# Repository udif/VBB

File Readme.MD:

VBB - A VCC Breakout Board
==========================
This board is intended as a VCC breakout board. It supports the following features:
* A wide array of connectors: USB A, B, Micro, Mini, DC plug, Banana Plug, screw terminal.
* While GND is always connected among all connectors, D+/D-/VCC are all switchable via pins.
* Banana plug dimensions match the front panel of Arachnid Lab's Re:Load Pro, and can be mounted directly on it, if one wishes.
* USB-A footprint can be soldered with either a male or female USB-A plug.

Possible uses:
--------------
1. Current measurements by inserting the Banana Plugs in the VCC path between any two connectors.
2. Power supply measurements using standard connectors (USB mini, micro, DC barrel jack) with Re:Load Pro 
3. Controlling of USB D+/D-, either disconnecting it to prevent a data connection, or biasing it with resistors to select a specific charging mode. Some Combinations, such as inserting VBB with two USB-A plugs (male+female) may require 2 PCBs.

TBD
---
* Add VCC/GND/D+/D- marks on the bottom side header pins.
* Possibly add mounting holes
* Next revision will be narrow and long, and support two independent USB-A connectors (male+female), one on each side.

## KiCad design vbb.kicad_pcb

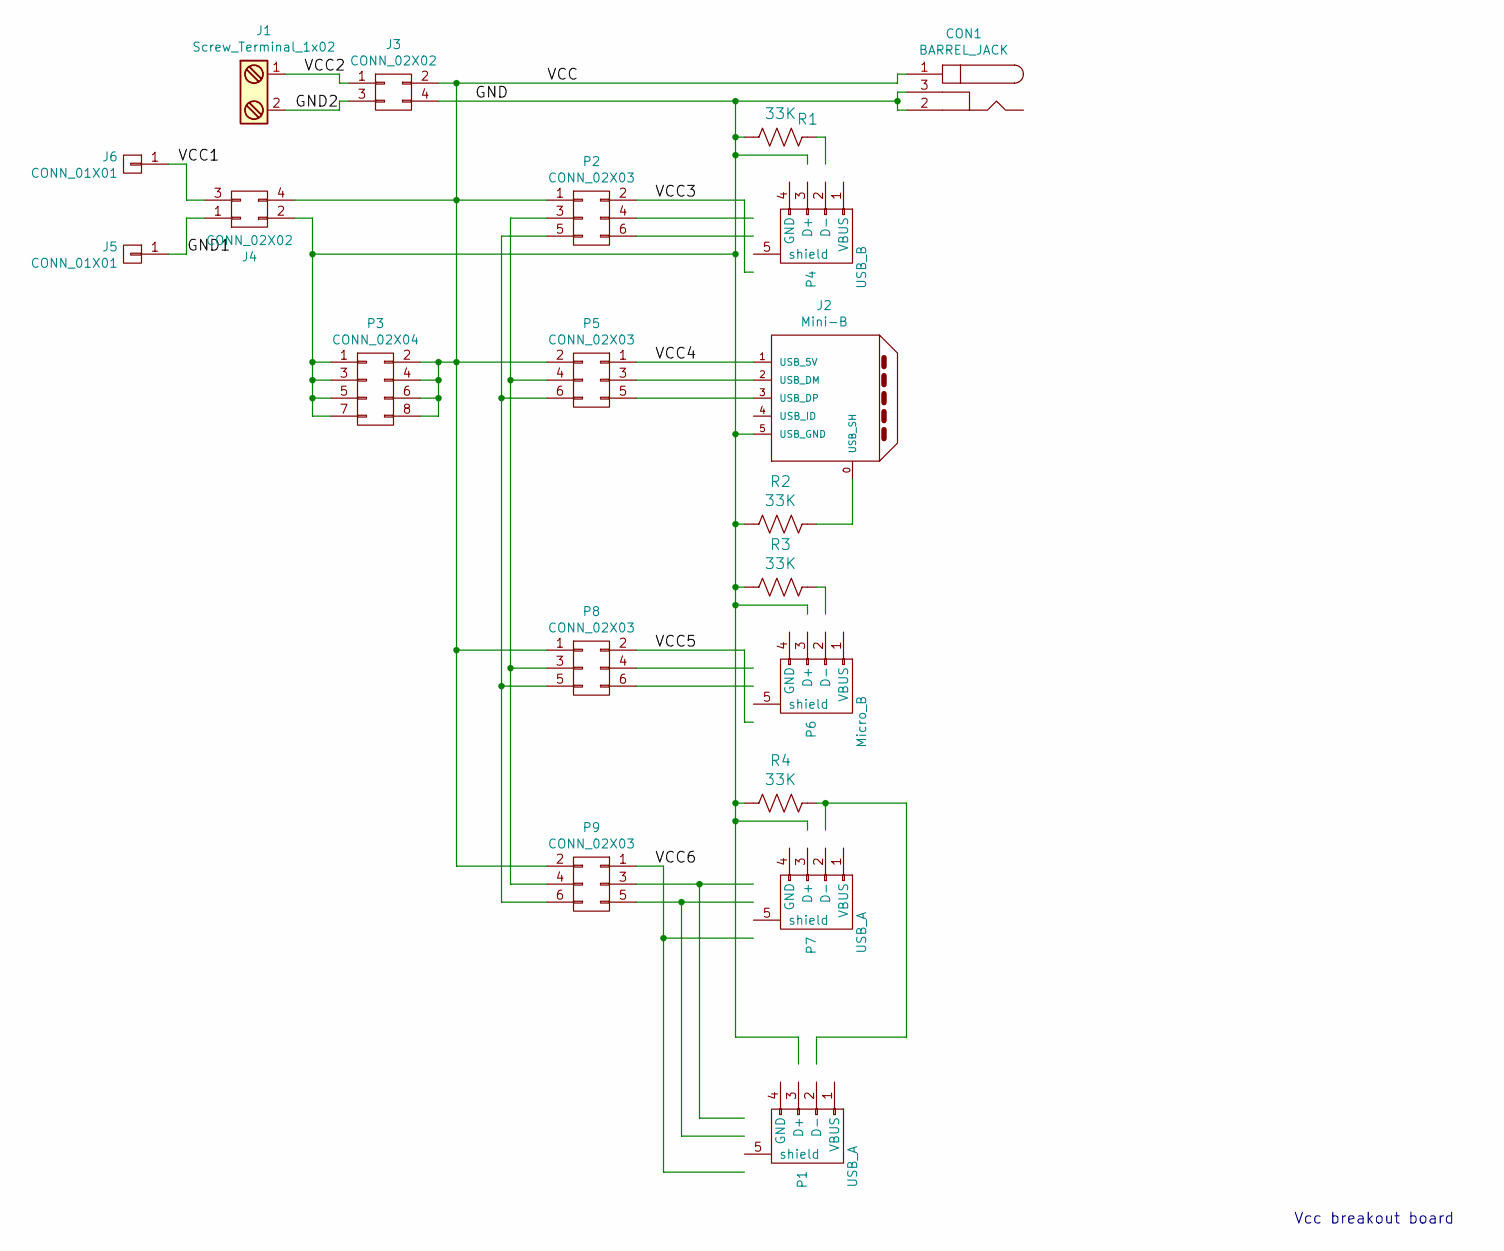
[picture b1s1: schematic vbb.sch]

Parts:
CON1: BARREL_JACK
J1: Screw_Terminal_1x02; TerminalBlock_Pheonix_MKDS1.5-2pol
J2: Mini-B; XM7D-0512
J3, J4: CONN_02X02; Pin_Header_Straight_2x02_Pitch2.54mm
J5, J6: CONN_01X01; Banana_Jack_1Pin
P1: USB_A; MOLEX-48037-0001
P2, P5, P8, P9: CONN_02X03; Pin_Header_Straight_2x03_Pitch2.54mm
P3: CONN_02X04; Pin_Header_Straight_2x04_Pitch2.54mm
P4: USB_B
P6: Micro_B; conn_usb_B_micro_smd
P7: USB_A
R1, R2, R3, R4: 33K; R_0805

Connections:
/GND: CON1.2, CON1.3, J2.5 (USB_GND), J3.4, J4.2, P1.4 (GND), P3.1, P3.3, P3.5, P3.7, P4.4 (GND), P6.4 (GND), P7.4 (GND), R1.1 (A), R2.1 (A), R3.1 (A), R4.1 (A)
/GND1: J4.1, J5.1
/GND2: J1.2, J3.3
/VCC: CON1.1, J3.2, J4.4, P2.1, P3.2, P3.4, P3.6, P3.8, P5.2, P8.1, P9.2
/VCC1: J4.3, J6.1
/VCC2: J1.1, J3.1
/VCC3: P2.2, P4.1 (VBUS)
/VCC4: J2.1 (USB_5V), P5.1
/VCC5: P6.1 (VBUS), P8.2
/VCC6: P1.1 (VBUS), P7.1 (VBUS), P9.1
unnamed: J2.0 (USB_SH), R2.2 (K)
unnamed: J2.2 (USB_DM), P5.3
unnamed: J2.3 (USB_DP), P5.5
unnamed: P1.2 (D-), P7.2 (D-), P9.3
unnamed: P1.3 (D+), P7.3 (D+), P9.5
unnamed: P1.5 (shield), P7.5 (shield), R4.2 (K)
unnamed: P2.3, P5.4, P8.3, P9.4
unnamed: P2.4, P4.2 (D-)
unnamed: P2.5, P5.6, P8.5, P9.6
unnamed: P2.6, P4.3 (D+)
unnamed: P4.5 (shield), R1.2 (K)
unnamed: P6.2 (D-), P8.4
unnamed: P6.3 (D+), P8.6
unnamed: P6.5 (shield), R3.2 (K)

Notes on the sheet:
Vcc breakout board

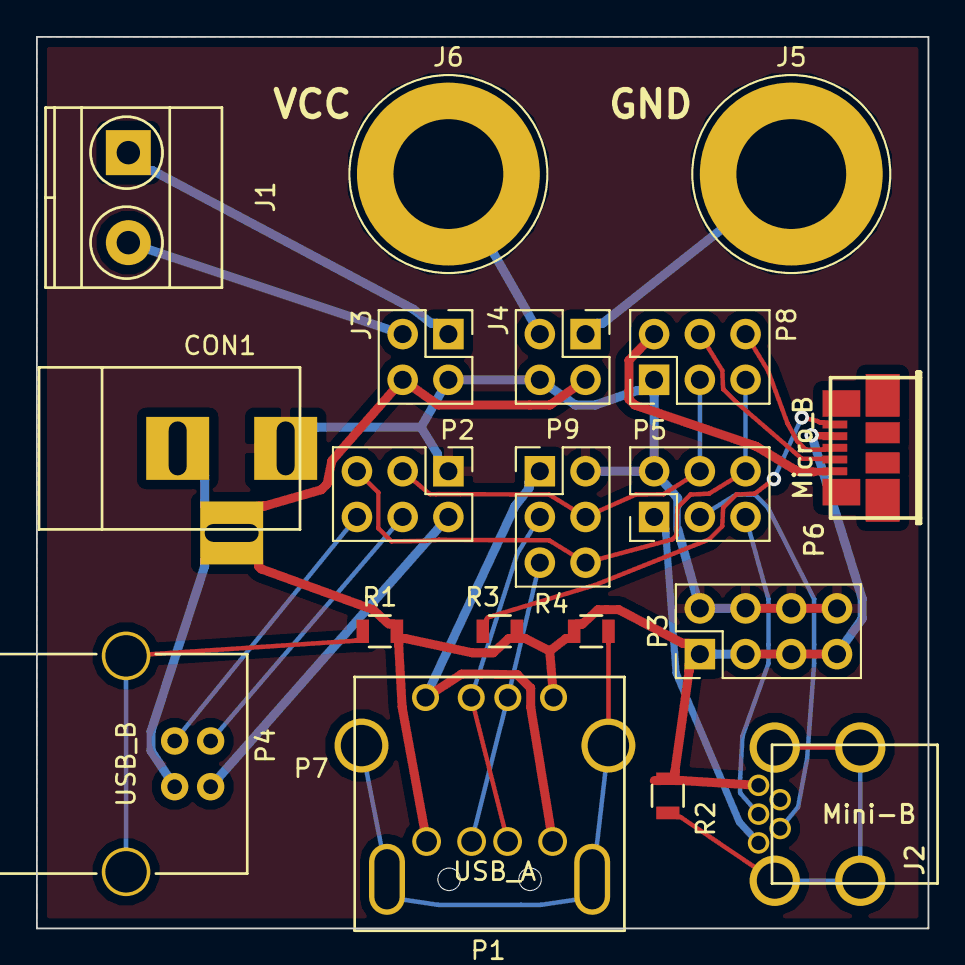
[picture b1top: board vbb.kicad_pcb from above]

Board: 2 copper layers, 49.5 x 49.5 mm, 20 parts (0 on the bottom side), 24 nets.

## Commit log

2016-11-26 Initial version
2016-11-26 Use Omron XM7D-0512 through hole USB mini connector
2016-11-27 Replaced old surface mount USB Mini with through hole Omron Mini-USB B through hole XM7D-0512
2016-11-27 Combined separate jumpers into a 2x03 connector As a result, board now fits the 50mmx50mm size group.
2016-11-29 Added missing ground wire.
2016-11-29 Use relative paths
2016-11-29 First pass through TopoR
2017-04-16 Files should be ready: Copper pours on both sides Added jumpers for current measurement Added silkscreen text VCC/GNC tracks are twice as wide.
2017-04-16 Fixes DRC by changing track-to-track clearance to 0.18mm and by deleting redundant multiple copper pours.
2017-04-21 Final (?) files. Swapped Banana jack pins on both PCB and schematics to have Red VCC, Black GND rendering. No actual layout change. Rearranged references on board Added VCC/GND marks on back side.
2017-04-21 Is this the final one? I think I haven't saved the schematics
2017-04-22 1st iteration of gerbers
2017-04-30 Files as delivered for manufacturing.
2017-04-30 Added README file and sample images
2017-05-16 Final files as manufactured
2017-05-16 Add files via upload
    Added actual picture
2017-05-16 Update Readme.MD
    Added a picture of the actual board.

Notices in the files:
vbb.kicad_pcb:
© 2017 Udi Finkelstein
